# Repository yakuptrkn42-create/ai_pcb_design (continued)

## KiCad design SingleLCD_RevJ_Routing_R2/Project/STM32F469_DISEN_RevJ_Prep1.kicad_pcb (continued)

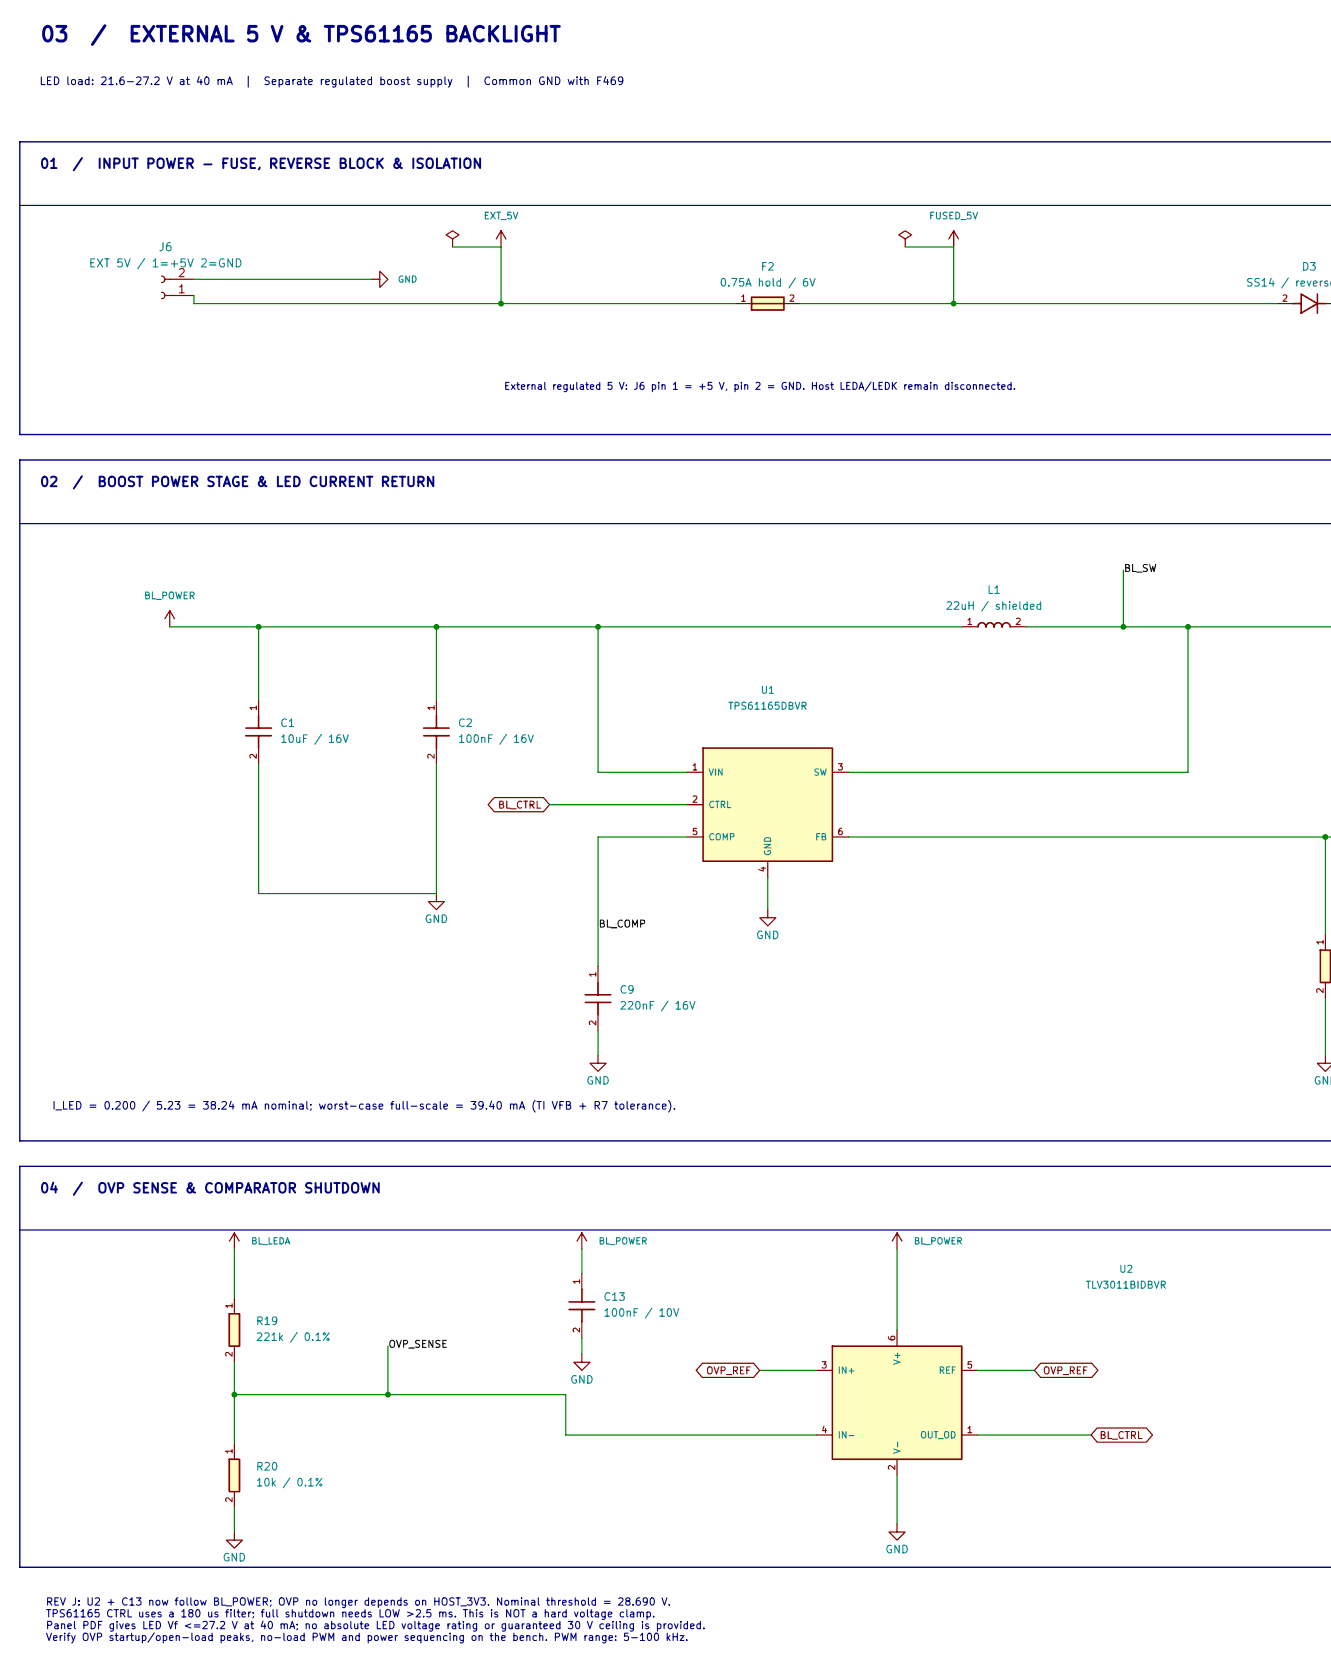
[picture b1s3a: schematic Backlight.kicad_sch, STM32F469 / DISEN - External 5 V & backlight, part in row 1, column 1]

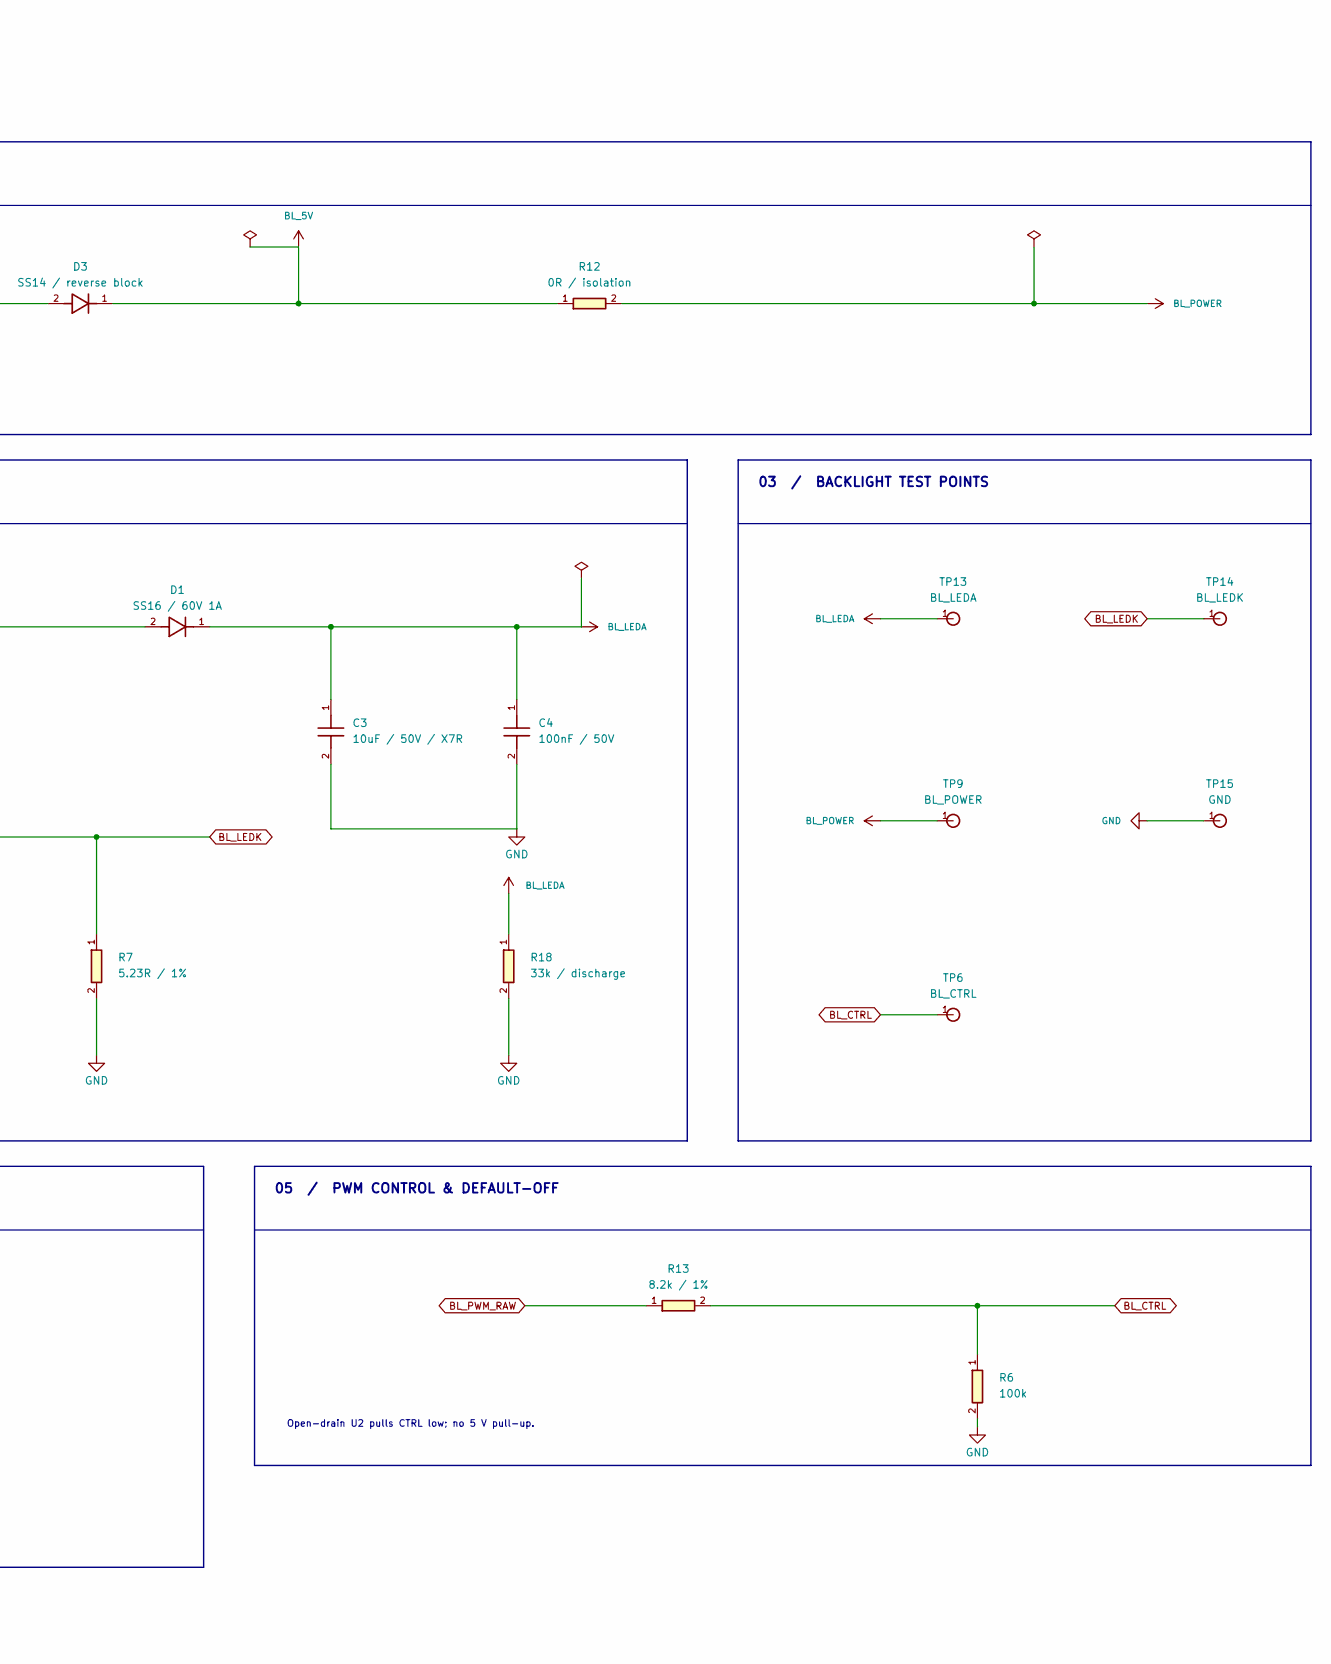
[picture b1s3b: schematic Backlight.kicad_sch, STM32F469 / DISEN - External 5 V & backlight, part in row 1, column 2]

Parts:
C1: 10uF / 16V; C_0805_2012Metric
C2: 100nF / 16V; C_0805_2012Metric
C3: 10uF / 50V / X7R; C_1210_3225Metric
C4: 100nF / 50V; C_0805_2012Metric
C9: 220nF / 16V; C_0805_2012Metric
C13: 100nF / 10V; C_0805_2012Metric
D1: SS16 / 60V 1A; D_SMA; MPN SS16
D3: SS14 / reverse block; D_SMA; MPN SS14
F2: 0.75A hold / 6V; Fuse_1206_3216Metric; MPN 1206L075/6YR
J6: EXT 5V / 1=+5V 2=GND; JST_NV_1x02_Existing
L1: 22uH / shielded; L_TDK_SLF7045; MPN SLF7045T-220M1R3-H
R6: 100k; R_0805_2012Metric
R7: 5.23R / 1%; R_0805_2012Metric
R12: 0R / isolation; R_0805_2012Metric
R13: 8.2k / 1%; R_0805_2012Metric
R18: 33k / discharge; R_0805_2012Metric
R19: 221k / 0.1%; R_0805_2012Metric
R20: 10k / 0.1%; R_0805_2012Metric
TP6: BL_CTRL; TestPoint_Pad_D1.0mm
TP9: BL_POWER; TestPoint_Pad_D1.0mm
TP13: BL_LEDA; TestPoint_Pad_D1.0mm
TP14: BL_LEDK; TestPoint_Pad_D1.0mm
TP15: GND; TestPoint_Pad_D1.0mm
U1: TPS61165DBVR; SOT-23-6; MPN TPS61165DBVR
U2: TLV3011BIDBVR; SOT-23-6; MPN TLV3011BIDBVR

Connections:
/Backlight / external power/BL_COMP: C9.1, U1.5 (COMP)
/Backlight / external power/BL_SW: D1.2 (A), L1.2, U1.3 (SW)
/Backlight / external power/OVP_SENSE: R19.2, R20.1, U2.4 (IN-)
BL_5V: D3.1 (K), R12.1
BL_CTRL: R6.1, R13.2, TP6.1, U1.2 (CTRL), U2.1 (OUT_OD)
BL_LEDA: C3.1, C4.1, D1.1 (K), R18.1, R19.1, TP13.1; also elsewhere on the board
BL_LEDK: R7.1, TP14.1, U1.6 (FB); also elsewhere on the board
BL_POWER: C1.1, C2.1, C13.1, L1.1, R12.2, TP9.1, U1.1 (VIN), U2.6 (V+)
BL_PWM_RAW: R13.1; also elsewhere on the board
EXT_5V: F2.1, J6.1
FUSED_5V: D3.2 (A), F2.2
GND: C1.2, C2.2, C3.2, C4.2, C9.2, C13.2, J6.2, R6.2, R7.2, R18.2, R20.2, TP15.1, U1.4 (GND), U2.2 (V-); also elsewhere on the board
OVP_REF: U2.3 (IN+), U2.5 (REF)

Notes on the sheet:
REV J: U2 + C13 now follow BL_POWER; OVP no longer depends on HOST_3V3. Nominal threshold = 28.690 V. TPS61165 CTRL uses a 180 us filter; full shutdown needs LOW >2.5 ms. This is NOT a hard voltage clamp. Panel PDF gives LED Vf <=27.2 V at 40 mA; no absolute LED voltage rating or guaranteed 30 V ce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
LED load: 21.6-27.2 V at 40 mA | Separate regulated boost supply | Common GND with F469
03 / EXTERNAL 5 V & TPS61165 BACKLIGHT
03 / BACKLIGHT TEST POINTS
I_LED = 0.200 / 5.23 = 38.24 mA nominal; worst-case full-scale = 39.40 mA (TI VFB + R7 tolerance).
External regulated 5 V: J6 pin 1 = +5 V, pin 2 = GND. Host LEDA/LEDK remain disconnected.
Open-drain U2 pulls CTRL low; no 5 V pull-up.
04 / OVP SENSE & COMPARATOR SHUTDOWN
01 / INPUT POWER - FUSE, REVERSE BLOCK & ISOLATION
02 / BOOST POWER STAGE & LED CURRENT RETURN
05 / PWM CONTROL & DEFAULT-OFF

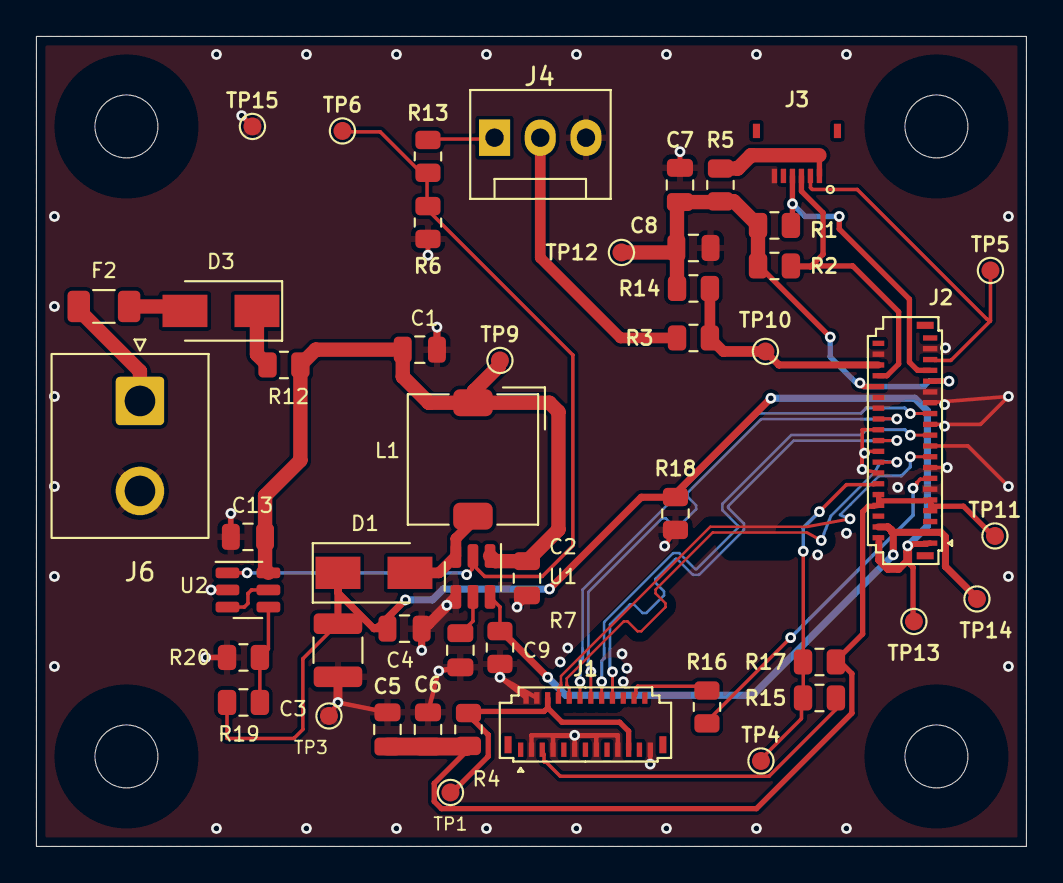
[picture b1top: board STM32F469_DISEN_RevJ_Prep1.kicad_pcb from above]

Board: 4 copper layers, 55.0 x 45.0 mm, 53 parts (0 on the bottom side), 32 nets.

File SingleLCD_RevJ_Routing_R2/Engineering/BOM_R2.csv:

Reference,Value,Footprint,Population,Selection_note
H1,MountingHole,Adapter_F469:MountingHole_3.5mm,FIT,
H2,MountingHole,Adapter_F469:MountingHole_3.5mm,FIT,
H3,MountingHole,Adapter_F469:MountingHole_3.5mm,FIT,
H4,MountingHole,Adapter_F469:MountingHole_3.5mm,FIT,
J1,FH26W-25S-0.3SHW(60),Adapter_F469:FH26W-25S-0.3SHW,FIT,"FPC pin1, contact side, thickness and exact ordering suffix require physical confirmation."
J2,FH26-39S-0.3SHW,Adapter_F469:FH26-39S-0.3SHW,FIT,"FPC pin1, contact side, thickness and exact ordering suffix require physical confirmation."
R3,100R,Adapter_F469:R_0805_2012Metric,FIT,
R14,10k,Adapter_F469:R_0805_2012Metric,FIT,
R15,100R,Adapter_F469:R_0805_2012Metric,FIT,
R16,0R,Adapter_F469:R_0805_2012Metric,FIT,
R17,10k,Adapter_F469:R_0805_2012Metric,FIT,
C5,4.7uF / 10V,Adapter_F469:C_0805_2012Metric,FIT,
C6,100nF / 10V,Adapter_F469:C_0805_2012Metric,FIT,
C7,1uF / 10V,Adapter_F469:C_0805_2012Metric,FIT,
C8,100nF / 10V,Adapter_F469:C_0805_2012Metric,FIT,
J3,FH19C-6S-0.5SH(10),Adapter_F469:FH19C-6S-0.5SH,FIT,"FPC pin1, contact side, thickness and exact ordering suffix require physical confirmation."
J4,HOST CTRL / 1=PC6 2=PB12 3=GND,Connector_Adapter:HostCtrl_1x03_Existing,FIT,
R1,4.7k / DNP,Adapter_F469:R_0805_2012Metric,DNP,
R2,4.7k / DNP,Adapter_F469:R_0805_2012Metric,DNP,
R4,0R,Adapter_F469:R_0805_2012Metric,FIT,
R5,0R,Adapter_F469:R_0805_2012Metric,FIT,Direct host3V3 touch supply is conditional on DISEN tolerance approval; do not energize panel before resolving report hold.
TP1,HOST_3V3,Adapter_F469:TestPoint_Pad_D1.0mm,FIT,
TP3,GND,Adapter_F469:TestPoint_Pad_D1.0mm,FIT,
TP4,LCD_RST,Adapter_F469:TestPoint_Pad_D1.0mm,FIT,
TP5,TP_INT,Adapter_F469:TestPoint_Pad_D1.0mm,FIT,
TP10,TP_RST,Adapter_F469:TestPoint_Pad_D1.0mm,FIT,
TP11,LCD_VCI,Adapter_F469:TestPoint_Pad_D1.0mm,FIT,
TP12,TP_VDD,Adapter_F469:TestPoint_Pad_D1.0mm,FIT,
C1,10uF / 16V,Adapter_F469:C_0805_2012Metric,FIT,
C2,100nF / 16V,Adapter_F469:C_0805_2012Metric,FIT,
C3,10uF / 50V / X7R,Adapter_F469:C_1210_3225Metric,FIT,X7R; effective capacitance at 30V must stay >=1uF; 50V rating; exact supplier curve required.
C4,100nF / 50V,Adapter_F469:C_0805_2012Metric,FIT,
C9,220nF / 16V,Adapter_F469:C_0805_2012Metric,FIT,
C13,100nF / 10V,Adapter_F469:C_0805_2012Metric,FIT,
D1,SS16 / 60V 1A,Adapter_F469:D_SMA,FIT,
D3,SS14 / reverse block,Adapter_F469:D_SMA,FIT,
F2,0.75A hold / 6V,Adapter_F469:Fuse_1206_3216Metric,FIT,"PPTC 0.75A hold, voltage >=6V; derating and fault current must be checked for the selected MPN."
J6,EXT 5V / 1=+5V 2=GND,Connector_Adapter:JST_NV_1x02_Existing,FIT,
L1,22uH / shielded,Adapter_F469:L_TDK_SLF7045,FIT,"22uH shielded; TDK SLF7045-H family reference. Legacy 220M1R3-H is discontinued; use verified stock or qualify an alternative. Irms >=0.6A engineering target, saturation/DC-bias curve must be checked."
R6,100k,Adapter_F469:R_0805_2012Metric,FIT,
R7,5.23R / 1%,Adapter_F469:R_0805_2012Metric,FIT,
R12,0R / isolation,Adapter_F469:R_0805_2012Metric,FIT,
R13,8.2k / 1%,Adapter_F469:R_0805_2012Metric,FIT,
R18,33k / discharge,Adapter_F469:R_0805_2012Metric,FIT,
R19,221k / 0.1%,Adapter_F469:R_0805_2012Metric,FIT,
R20,10k / 0.1%,Adapter_F469:R_0805_2012Metric,FIT,
TP6,BL_CTRL,Adapter_F469:TestPoint_Pad_D1.0mm,FIT,
TP9,BL_POWER,Adapter_F469:TestPoint_Pad_D1.0mm,FIT,
TP13,BL_LEDA,Adapter_F469:TestPoint_Pad_D1.0mm,FIT,
TP14,BL_LEDK,Adapter_F469:TestPoint_Pad_D1.0mm,FIT,
TP15,GND,Adapter_F469:TestPoint_Pad_D1.0mm,FIT,
U1,TPS61165DBVR,Adapter_F469:SOT-23-6,FIT,
U2,TLV3011BIDBVR,Adapter_F469:SOT-23-6,FIT,TLV3011BIDBVR only; do not silently substitute non-B or push-pull TLV3012.

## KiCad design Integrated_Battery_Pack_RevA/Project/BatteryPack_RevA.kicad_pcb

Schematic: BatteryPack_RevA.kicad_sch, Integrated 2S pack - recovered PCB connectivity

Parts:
C1: 100nF/50V; FP_C1
C2: 100nF/16V; FP_C2
C4: 2.2µF/16V; FP_C4
C5: 100nF/16V; FP_C5
C6: 100nF/16V; FP_C6
C7: 100nF/50V; FP_C7
C11: 100nF/16V; FP_C11
C12: 100nF/16V; FP_C12
C13: 100nF/16V; FP_C13
C14: 100nF/16V; FP_C14
C16: 1µF/16V; FP_C16
C17: 100nF/16V; FP_C17
C20: 100nF/16V; FP_C20
D1: BAS16-7-F; FP_D1
D2: MM3Z5V6C; FP_D2
D3: MM3Z5V6C; FP_D3
F1: 2.5A_1206_FUSE_TBD; FP_F1
F2: 0.5A_FAST_1206_FUSE_TBD; FP_F2
J1: CZX-4B2-2.54-e_FIXED; FP_J1
J12: Solder_JMP_1; FP_J12
PAD1: TH/Rec2.7x5.4_R1.8; FP_PAD1
PAD3: SMD/Rec1.5x3.0; FP_PAD3
PAD4: SMD/Rec1.5x3.0; FP_PAD4
PAD7: TH/Rec2.7x5.4_R1.8; FP_PAD7
PAD8: TH/Rec2.7x5.4_R1.8; FP_PAD8
PAD17: PAD; FP_PAD17
PAD19: PAD; FP_PAD19
Pad2: Pad; FP_Pad2
Pad5: Pad; FP_Pad5
Pad6: Pad; FP_Pad6
Pad9: Pad; FP_Pad9
Pad10: Pad; FP_Pad10
Pad11: Pad; FP_Pad11
Pad12: Pad; FP_Pad12
Pad13: Pad; FP_Pad13
Q1: SI1414DH-T1-GE3; FP_Q1
Q2: CSD16412Q5A; FP_Q2
Q3: CSD16412Q5A; FP_Q3
Q4: 2N7002K_R1_00001; FP_Q4
R1: 100R; FP_R1
R2: 100R; FP_R2
R3: 5.1k; FP_R3
R4: 10M; FP_R4
R5: 1mR; FP_R5
R6: 5.1k; FP_R6
R7: 10R; FP_R7
R8: 5.1k; FP_R8
R11: 100R; FP_R11
R12: 100R; FP_R12
R13: 10M; FP_R13
R14: 100k; FP_R14
R15: 5.1k; FP_R15
R20: 1k; FP_R20
R21: 100R; FP_R21
R22: 100R; FP_R22
R24: 1k; FP_R24
R26: 100R; FP_R26
R27: 4.99R; FP_R27
R28: 1k; FP_R28
R29: 100R; FP_R29
R30: 1k; FP_R30
R32: 100k; FP_R32
R40: 0.1R_1%_1206; FP_R40
R46: Net-Tie; FP_R46
TH1: 10k_NTC_BEAD_BETA_TBD; FP_TH1
TH2: 10k_NTC_BEAD_BETA_TBD; FP_TH2
U1: BQ294502DRVR; FP_U1
U2: BQ28Z610DRZR-R1; FP_U2
U3: SCF4030-12-02; FP_U3
WIRE1: AWG10; FP_WIRE1
WIRE2: AWG10; FP_WIRE2
WIRE3: AWG10; FP_WIRE3
WIRE6: AWG10; FP_WIRE6

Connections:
AUX_PRE_FUSE: F2.1 (PAD_1), R40.2 (PAD_2)
BMS_TS: PAD3.PAD, TH1.1 (PAD_1), U2.4 (PAD_4)
CELL_MID: PAD1.PAD, R3.1 (PAD_1), R8.1 (PAD_1), R20.2 (PAD_2), R26.1 (PAD_1)
CELL_MINUS: C4.2 (PAD_2), C11.2 (PAD_2), C13.2 (PAD_2), C14.2 (PAD_2), C17.2 (PAD_2), C20.2 (PAD_2), PAD4.PAD, PAD8.PAD, PAD17.17, PAD19.17, Q1.4 (PAD_4), R5.1 (PAD_1), R22.2 (PAD_2), R32.1 (PAD_1), R46.1 (PAD_1), R46.2 (PAD_2), TH1.2 (PAD_2), U1.3 (PAD_3), U1.7 (PAD_7), U2.1 (PAD_1), U2.13 (PAD_13)
CELL_PLUS: PAD7.PAD, R27.1 (PAD_1), R28.2 (PAD_2), R29.2 (PAD_2), U3.2 (PAD_2)
DRAIN: Pad2.1, Pad5.1, Pad6.1, Pad9.1, Pad10.1, Pad11.1, Pad12.1, Pad13.1, Q2.5 (PAD_5), Q2.6 (PAD_6), Q2.7 (PAD_7), Q2.8 (PAD_8), Q2.9 (PAD_9), Q3.5 (PAD_5), Q3.6 (PAD_6), Q3.7 (PAD_7), Q3.8 (PAD_8), Q3.9 (PAD_9)
FuseOut: C7.2 (PAD_2), Q3.1 (PAD_1), Q3.2 (PAD_2), Q3.3 (PAD_3), R13.1 (PAD_1), R24.2 (PAD_2), U3.1 (PAD_1)
G: C20.1 (PAD_1), Q1.3 (PAD_3), R30.1 (PAD_1), R32.2 (PAD_2)
HOST_NTC: J1.3 (PAD_3), TH2.1 (PAD_1)
Net_1: C5.2 (PAD_2), C6.1 (PAD_1)
Net_4: D3.1 (PAD_1), R1.2 (PAD_2), R12.1 (PAD_1)
Net_5: D2.1 (PAD_1), R2.2 (PAD_2), R11.1 (PAD_1)
Net_8: R12.2 (PAD_2), U2.5 (PAD_5)
Net_9: R11.2 (PAD_2), U2.6 (PAD_6)
Net_12: C1.2 (PAD_2), C7.1 (PAD_1)
Net_13: Q2.4 (PAD_4), Q4.3 (PAD_3), R4.1 (PAD_1), R6.2 (PAD_2)
Net_14: Q3.4 (PAD_4), R13.2 (PAD_2), R15.2 (PAD_2)
Net_15: D1.3 (PAD_3), R7.2 (PAD_2)
Net_16: R7.1 (PAD_1), U2.8 (PAD_8)
Net_17: R6.1 (PAD_1), U2.7 (PAD_7)
Net_18: Q4.1 (PAD_1), R14.2 (PAD_2)
Net_19: R15.1 (PAD_1), U2.9 (PAD_9)
Net_20: J12.1 (PAD_1), R24.1 (PAD_1)
Net_24: C4.1 (PAD_1), U2.10 (PAD_10)
Net_33: C12.2 (PAD_2), C14.1 (PAD_1), R22.1 (PAD_1), U2.3 (PAD_3)
Net_34: C12.1 (PAD_1), C13.1 (PAD_1), R21.1 (PAD_1), U2.2 (PAD_2)
Net_40: C16.1 (PAD_1), R27.2 (PAD_2), U2.11 (PAD_11)
Net_41: C11.1 (PAD_1), C16.2 (PAD_2), R26.2 (PAD_2), U2.12 (PAD_12)
Net_42: C2.1 (PAD_1), C17.1 (PAD_1), R20.1 (PAD_1), U1.4 (PAD_4)
Net_43: C2.2 (PAD_2), R28.1 (PAD_1), U1.1 (PAD_1), U1.2 (PAD_2)
Net_44: R29.1 (PAD_1), U1.5 (PAD_5)
Net_45: R30.2 (PAD_2), U1.6 (PAD_6)
Net_46: Q1.1 (PAD_1), Q1.2 (PAD_2), Q1.5 (PAD_5), Q1.6 (PAD_6), U3.3 (PAD_3)
PACK_MINUS: C6.2 (PAD_2), D2.2 (PAD_2), D3.2 (PAD_2), J1.4 (PAD_4), R5.2 (PAD_2), R14.1 (PAD_1), R21.2 (PAD_2), TH2.2 (PAD_2), WIRE6.WIRE
PACK_PLUS: F1.2 (PAD_2), J1.1 (PAD_1), R40.1 (PAD_1)
PACK_PLUS_AUX: F2.2 (PAD_2), J1.2 (PAD_2)
PROTECTED_PLUS: C1.1 (PAD_1), C5.1 (PAD_1), D1.1 (PAD_1), F1.1 (PAD_1), J12.2 (PAD_2), Q2.1 (PAD_1), Q2.2 (PAD_2), Q2.3 (PAD_3), Q4.2 (PAD_2), R4.2 (PAD_2), WIRE3.WIRE
SCL: R1.1 (PAD_1), R3.2 (PAD_2), WIRE1.WIRE
SDA: R2.1 (PAD_1), R8.2 (PAD_2), WIRE2.WIRE

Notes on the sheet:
CONNECTIVITY RECOVERED FROM PCB - PASSIVE PAD SYMBOLS; NOT FUNCTIONALLY VERIFIED. DESIGNER REVIEW REQUIRED.

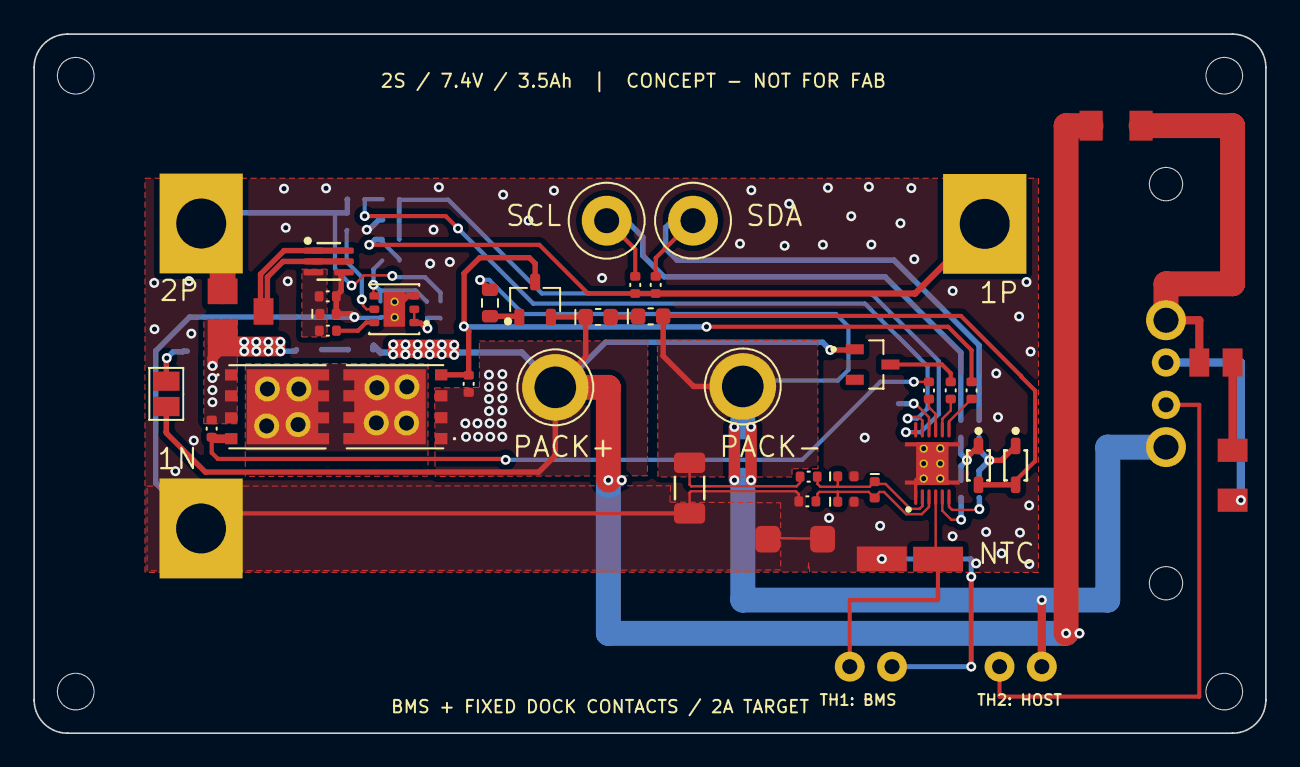
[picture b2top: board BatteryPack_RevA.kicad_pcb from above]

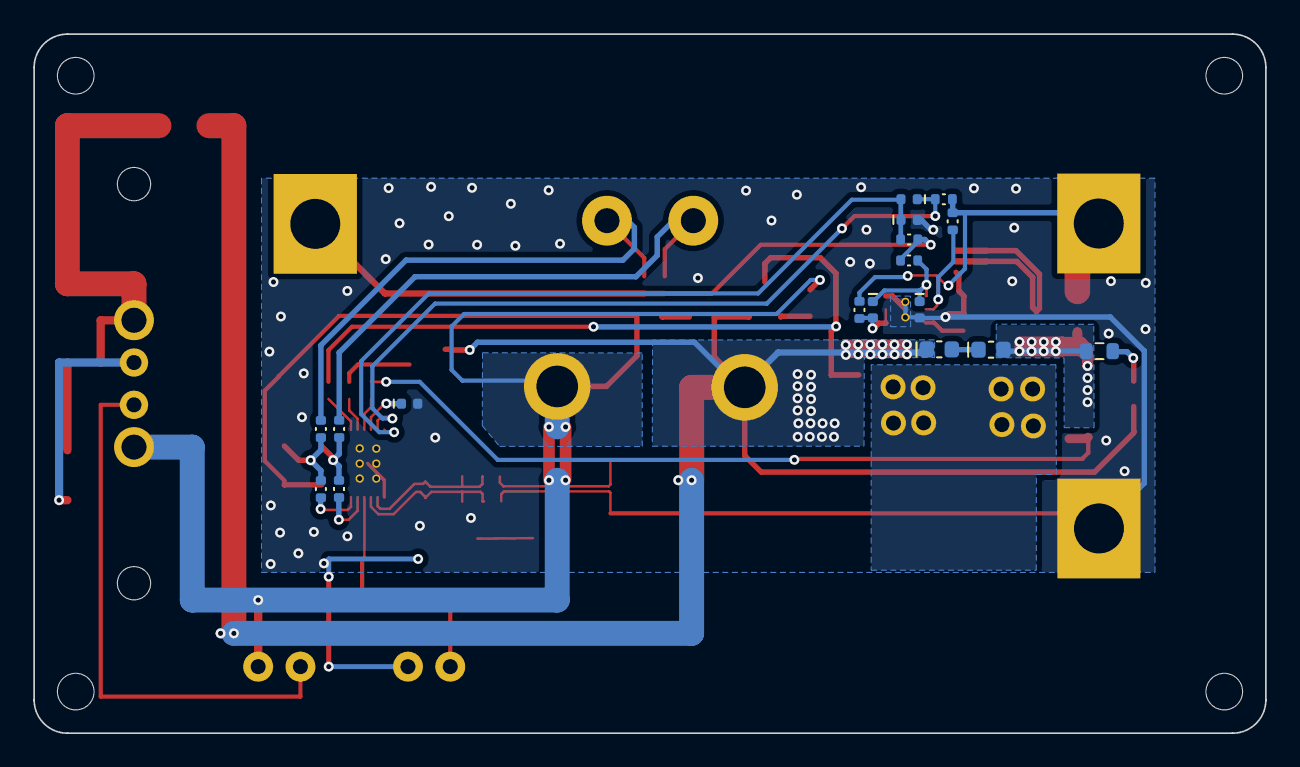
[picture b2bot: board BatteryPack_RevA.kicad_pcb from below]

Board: 2 copper layers, 74.0 x 42.0 mm, 78 parts (17 on the bottom side), 39 nets.

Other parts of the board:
H1: M2 NPTH; FP_H1
H2: M2 NPTH; FP_H2
H3: M2 NPTH; FP_H3
H4: M2 NPTH; FP_H4
MECH1: 2x18650_CARRIER_REFERENCE; FP_MECH1

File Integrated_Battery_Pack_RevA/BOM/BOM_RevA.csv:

Reference,Value / candidate,Qty,Footprint,Status / verification
TH2,10k_NTC_BEAD_BETA_TBD,1,BatteryPack:FP_TH2,NEW CONCEPT; exact part and assembly qualification pending
TH1,10k_NTC_BEAD_BETA_TBD,1,BatteryPack:FP_TH1,NEW CONCEPT; exact part and assembly qualification pending
F2,0.5A_FAST_1206_FUSE_TBD,1,BatteryPack:FP_F2,NEW CONCEPT; exact part and assembly qualification pending
R40,0.1R_1%_1206,1,BatteryPack:FP_R40,NEW CONCEPT; exact part and assembly qualification pending
F1,2.5A_1206_FUSE_TBD,1,BatteryPack:FP_F1,NEW CONCEPT; exact part and assembly qualification pending
J1,CZX-4B2-2.54-e_FIXED,1,BatteryPack:FP_J1,NEW CONCEPT; exact part and assembly qualification pending
U2,BQ28Z610DRZR-R1,1,BatteryPack:FP_U2,Original PCB value; manufacturer pinout and ratings NOT requalified
R7,10R,1,BatteryPack:FP_R7,Original PCB value; manufacturer pinout and ratings NOT requalified
U1,BQ294502DRVR,1,BatteryPack:FP_U1,Original PCB value; manufacturer pinout and ratings NOT requalified
Q3,CSD16412Q5A,1,BatteryPack:FP_Q3,Original PCB value; manufacturer pinout and ratings NOT requalified
R15,5.1k,1,BatteryPack:FP_R15,Original PCB value; manufacturer pinout and ratings NOT requalified
U3,SCF4030-12-02,1,BatteryPack:FP_U3,Original PCB value; manufacturer pinout and ratings NOT requalified
R14,100k,1,BatteryPack:FP_R14,Original PCB value; manufacturer pinout and ratings NOT requalified
C14,100nF/16V,1,BatteryPack:FP_C14,Original PCB value; manufacturer pinout and ratings NOT requalified
R5,1mR,1,BatteryPack:FP_R5,Original PCB value; manufacturer pinout and ratings NOT requalified
R13,10M,1,BatteryPack:FP_R13,Original PCB value; manufacturer pinout and ratings NOT requalified
C6,100nF/16V,1,BatteryPack:FP_C6,Original PCB value; manufacturer pinout and ratings NOT requalified
R30,1k,1,BatteryPack:FP_R30,Original PCB value; manufacturer pinout and ratings NOT requalified
C20,100nF/16V,1,BatteryPack:FP_C20,Original PCB value; manufacturer pinout and ratings NOT requalified
R21,100R,1,BatteryPack:FP_R21,Original PCB value; manufacturer pinout and ratings NOT requalified
Q1,SI1414DH-T1-GE3,1,BatteryPack:FP_Q1,Original PCB value; manufacturer pinout and ratings NOT requalified
C5,100nF/16V,1,BatteryPack:FP_C5,Original PCB value; manufacturer pinout and ratings NOT requalified
R6,5.1k,1,BatteryPack:FP_R6,Original PCB value; manufacturer pinout and ratings NOT requalified
D2,MM3Z5V6C ,1,BatteryPack:FP_D2,Original PCB value; manufacturer pinout and ratings NOT requalified
R32,100k,1,BatteryPack:FP_R32,Original PCB value; manufacturer pinout and ratings NOT requalified
R22,100R,1,BatteryPack:FP_R22,Original PCB value; manufacturer pinout and ratings NOT requalified
D1,BAS16-7-F,1,BatteryPack:FP_D1,Original PCB value; manufacturer pinout and ratings NOT requalified
R8,5.1k,1,BatteryPack:FP_R8,Original PCB value; manufacturer pinout and ratings NOT requalified
Q2,CSD16412Q5A,1,BatteryPack:FP_Q2,Original PCB value; manufacturer pinout and ratings NOT requalified
Q4,2N7002K_R1_00001,1,BatteryPack:FP_Q4,Original PCB value; manufacturer pinout and ratings NOT requalified
R4,10M,1,BatteryPack:FP_R4,Original PCB value; manufacturer pinout and ratings NOT requalified
D3,MM3Z5V6C ,1,BatteryPack:FP_D3,Original PCB value; manufacturer pinout and ratings NOT requalified
C13,100nF/16V,1,BatteryPack:FP_C13,Original PCB value; manufacturer pinout and ratings NOT requalified
R3,5.1k,1,BatteryPack:FP_R3,Original PCB value; manufacturer pinout and ratings NOT requalified
C12,100nF/16V,1,BatteryPack:FP_C12,Original PCB value; manufacturer pinout and ratings NOT requalified
R26,100R,1,BatteryPack:FP_R26,Original PCB value; manufacturer pinout and ratings NOT requalified
R2,100R,1,BatteryPack:FP_R2,Original PCB value; manufacturer pinout and ratings NOT requalified
C4,2.2µF/16V,1,BatteryPack:FP_C4,Original PCB value; manufacturer pinout and ratings NOT requalified
C11,100nF/16V,1,BatteryPack:FP_C11,Original PCB value; manufacturer pinout and ratings NOT requalified
R11,100R,1,BatteryPack:FP_R11,Original PCB value; manufacturer pinout and ratings NOT requalified
R24,1k,1,BatteryPack:FP_R24,Original PCB value; manufacturer pinout and ratings NOT requalified
R29,100R,1,BatteryPack:FP_R29,Original PCB value; manufacturer pinout and ratings NOT requalified
C7,100nF/50V,1,BatteryPack:FP_C7,Original PCB value; manufacturer pinout and ratings NOT requalified
R1,100R,1,BatteryPack:FP_R1,Original PCB value; manufacturer pinout and ratings NOT requalified
C1,100nF/50V,1,BatteryPack:FP_C1,Original PCB value; manufacturer pinout and ratings NOT requalified
R20,1k,1,BatteryPack:FP_R20,Original PCB value; manufacturer pinout and ratings NOT requalified
R28,1k,1,BatteryPack:FP_R28,Original PCB value; manufacturer pinout and ratings NOT requalified
R27,4.99R,1,BatteryPack:FP_R27,Original PCB value; manufacturer pinout and ratings NOT requalified
C16,1µF/16V,1,BatteryPack:FP_C16,Original PCB value; manufacturer pinout and ratings NOT requalified
R12,100R,1,BatteryPack:FP_R12,Original PCB value; manufacturer pinout and ratings NOT requalified
C2,100nF/16V,1,BatteryPack:FP_C2,Original PCB value; manufacturer pinout and ratings NOT requalified
C17,100nF/16V,1,BatteryPack:FP_C17,Original PCB value; manufacturer pinout and ratings NOT requalified
"CELL1,CELL2",18650 3.7 V 3500 mAh,2,Mechanical,"Brand/model, max dimensions and 2A rating pending"
CARRIER,PA66-GF insulated carrier,1,Mechanical,Concept material; tolerance/flame/creep qualification pending
STRAPS,Non-conductive retention bands + compliant pads,2,Mechanical,Retention force and cell wrapper protection pending
NICKEL,Pure Ni 0.15 x 6 mm with formed pre-tinned 2.5 mm solder tongue,3,Mechanical,Process coupon and weld pull-test required
INSULATION,0.4 mm fishpaper + insulating terminal rings and tab sleeves,1,Mechanical,Dielectric and abrasion qualification pending
M2,Insulated M2 PCB fastener set,4,Mechanical,Length/torque TBD
M1.6,Dock flange fastener set,2,Mechanical,Supplier flange drawing and actual sample check required
